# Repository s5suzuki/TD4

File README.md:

# TD4

- 「CPUの創りかた」のCPUの基板データとLチカプログラム
  - ROM部分は面倒なのでRaspberry Pi Picoで代用している

# Author

Shun Suzuki, 2023

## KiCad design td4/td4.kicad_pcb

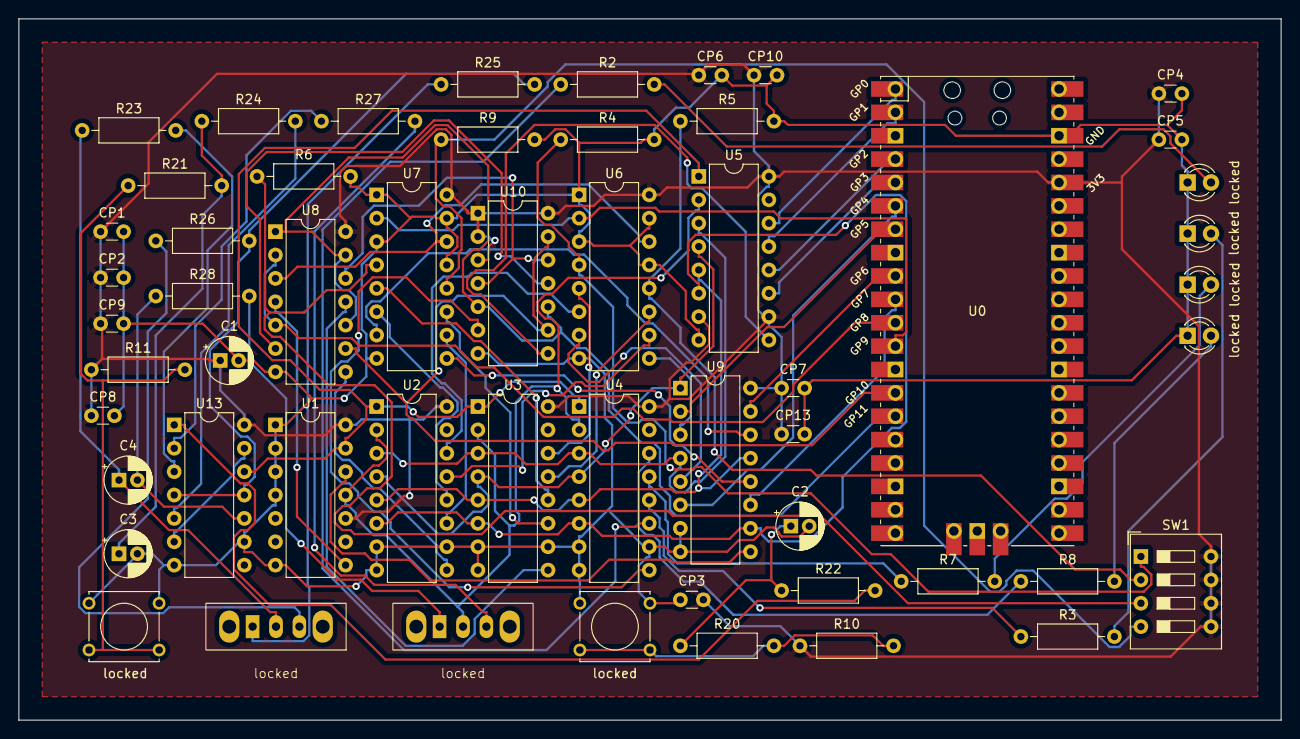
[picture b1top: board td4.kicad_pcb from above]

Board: 2 copper layers, 137.2 x 76.2 mm, 55 parts (0 on the bottom side), 69 nets.

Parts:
C1: 100u; CP_Radial_D5.0mm_P2.00mm
C2, C3, C4: 10u; CP_Radial_D5.0mm_P2.00mm
CP1, CP2, CP3, CP4, CP5, CP6, CP7, CP8, CP9, CP10, CP13: 0.1u; C_Disc_D3.0mm_W1.6mm_P2.50mm
R2, R3, R4, R5, R6, R7, R8, R9, R10, R11: 1k; R_Axial_DIN0207_L6.3mm_D2.5mm_P10.16mm_Horizontal
R20: 10k; R_Axial_DIN0207_L6.3mm_D2.5mm_P10.16mm_Horizontal
R21, R22, R23, R24: 100k; R_Axial_DIN0207_L6.3mm_D2.5mm_P10.16mm_Horizontal
R25: 3.3k; R_Axial_DIN0207_L6.3mm_D2.5mm_P10.16mm_Horizontal
R26: 33k; R_Axial_DIN0207_L6.3mm_D2.5mm_P10.16mm_Horizontal
R27, R28: 100; R_Axial_DIN0207_L6.3mm_D2.5mm_P10.16mm_Horizontal
SW1: SW_DIP_x04; SW_DIP_SPSTx04_Slide_9.78x12.34mm_W7.62mm_P2.54mm
U0: Pico; RPi_Pico_SMD_TH
U1: 74HC74; DIP-14_W7.62mm
U2, U3, U4, U5: 74LS161; DIP-16_W7.62mm
U6, U7: 74HC153; DIP-16_W7.62mm
U8: 74LS32; DIP-14_W7.62mm
U9: 74HC283; DIP-16_W7.62mm
U10: 74LS10; DIP-14_W7.62mm
U13: 74HC14; DIP-14_W7.62mm
locked: LED; LED_D3.0mm
locked#2, locked#5, locked#6: LED; LED_D3.0mm
locked#3, locked#7: SW_SPDT; Toggle_Switch
locked#4, locked#8: SW_MEC_5E; SW_Tactile_Straight_KSL0Axx1LFTR

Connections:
+3.3V: C1.1, CP1.1, CP2.1, CP3.2, CP4.1, CP5.1, CP6.1, CP7.1, CP8.1, CP9.1, CP10.1, CP13.1, R10.1, R11.1, SW1.5, SW1.6, SW1.7, SW1.8, U0.36 (3V3), U1.10 (~S), U1.14 (VCC), U2.16 (VCC), U3.16 (VCC), U4.16 (VCC), U5.7 (ENP), U5.10 (ENT), U5.16 (VCC), U6.16 (VCC), U7.16 (VCC), U8.14 (VCC), U9.16 (VCC), U10.1, U10.2, U10.3, U10.14 (VCC), U13.14 (VCC)
/clock_reset/CLOCK: U1.11 (C), U2.2 (CK), U3.2 (CK), U4.2 (CK), U5.2 (CK), locked#3.2 (B)
/clock_reset/RESET: U1.13 (~R), U2.1 (~CLR), U3.1 (~CLR), U4.1 (~CLR), U5.1 (~CLR), U13.12
/logic/A0: U0.1 (GPIO0), U5.14 (QA)
/logic/A1: U0.2 (GPIO1), U5.13 (QB)
/logic/A2: U0.4 (GPIO2), U5.12 (QC)
/logic/A3: U0.5 (GPIO3), U5.11 (QD)
/logic/D0: U0.6 (GPIO4), U9.6 (B1)
/logic/D1: U0.7 (GPIO5), U9.2 (B2)
/logic/D2: U0.9 (GPIO6), U9.15 (B3)
/logic/D3: U0.10 (GPIO7), U9.11 (B4)
/logic/D4: U0.11 (GPIO8), U8.2, U8.5
/logic/D5: U0.12 (GPIO9), U6.2 (B), U7.2 (B)
/logic/D6: U0.14 (GPIO10), U8.9, U10.9, U10.13
/logic/D7: U0.15 (GPIO11), U8.1, U8.10, U8.13, U10.5, U10.10
GND: C1.2, C2.2, C3.2, CP1.2, CP2.2, CP3.1, CP4.2, CP5.2, CP6.2, CP7.2, CP8.2, CP9.2, CP10.2, CP13.2, R4.2, R5.2, R6.2, R9.2, U0.38 (GND), U1.1 (~R), U1.2 (D), U1.3 (C), U1.4 (~S), U1.7 (GND), U2.7 (ENP), U2.8 (GND), U2.10 (ENT), U3.7 (ENP), U3.8 (GND), U3.10 (ENT), U4.7 (ENP), U4.8 (GND), U4.10 (ENT), U5.8 (GND), U6.1 (~1G), U6.3 (IC3), U6.8 (GND), U6.13 (2C3), U6.15 (~2G), U7.1 (~1G), U7.3 (IC3), U7.8 (GND), U7.13 (2C3), U7.15 (~2G), U8.7 (GND), U9.7 (C0), U9.8 (GND), U10.7 (GND), U13.7 (GND), U13.9, locked.1 (K), locked#2.1 (K), locked#4.1, locked#5.1 (K), locked#6.1 (K), locked#8.1
unnamed: C2.1, R20.1, R22.1
unnamed: C3.1, R21.2, R24.1
unnamed: C4.2, R28.1, U13.10
unnamed: R2.2, locked#5.2 (A)
unnamed: R3.2, locked.2 (A)
unnamed: R7.2, locked#2.2 (A)
unnamed: R8.2, locked#6.2 (A)
unnamed: R22.2, U13.1
unnamed: R23.2, U13.3
unnamed: R24.2, U13.5
unnamed: R25.2, R26.2, U13.4, U13.11
unnamed: R27.1, U13.2
unnamed: R10.2, R20.2, locked#8.2 (A)
unnamed: R11.2, R21.1, locked#4.2 (A)
unnamed: R25.1, locked#7.1 (A)
unnamed: C4.1, R23.1, locked#7.2 (B)
unnamed: R26.1, locked#7.3 (C)
unnamed: R28.2, locked#3.1 (A)
unnamed: R27.2, locked#3.3 (C)
unnamed: U1.12 (D), U9.9 (C4)
unnamed: U1.8 (~Q), U8.4
unnamed: U2.3 (A), U3.3 (A), U4.3 (A), U5.3 (A), U9.4 (S1)
unnamed: U2.4 (B), U3.4 (B), U4.4 (B), U5.4 (B), U9.1 (S2)
unnamed: U2.5 (C), U3.5 (C), U4.5 (C), U5.5 (C), U9.13 (S3)
unnamed: U2.6 (D), U3.6 (D), U4.6 (D), U5.6 (D), U9.10 (S4)
unnamed: U2.14 (QA), U6.6 (IC0)
unnamed: U2.13 (QB), U6.10 (2C0)
unnamed: U2.12 (QC), U7.6 (IC0)
unnamed: U2.11 (QD), U7.10 (2C0)
unnamed: U2.9 (~LOAD), U8.8
unnamed: U3.14 (QA), U6.5 (IC1)
unnamed: U3.13 (QB), U6.11 (2C1)
unnamed: U3.12 (QC), U7.5 (IC1)
unnamed: U3.11 (QD), U7.11 (2C1)
unnamed: U3.9 (~LOAD), U8.11
unnamed: R8.1, U4.14 (QA)
unnamed: R7.1, U4.13 (QB)
unnamed: R3.1, U4.12 (QC)
unnamed: R2.1, U4.11 (QD)
unnamed: U4.9 (~LOAD), U10.6
unnamed: U5.9 (~LOAD), U10.8
unnamed: U6.7 (1Y), U9.5 (A1)
unnamed: R5.1, SW1.2, U6.12 (2C2)
unnamed: U6.9 (2Y), U9.3 (A2)
unnamed: U6.14 (A), U7.14 (A), U8.3
unnamed: R4.1, SW1.1, U6.4 (IC2)
unnamed: U7.7 (1Y), U9.14 (A3)
unnamed: R9.1, SW1.4, U7.12 (2C2)
unnamed: U7.9 (2Y), U9.12 (A4)
unnamed: R6.1, SW1.3, U7.4 (IC2)
unnamed: U8.6, U10.11
unnamed: U8.12, U10.4, U10.12
unnamed: U13.6, U13.13

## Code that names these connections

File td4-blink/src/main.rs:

//! Blinks the LED on a Pico board
//!
//! This will blink an LED attached to GP25, which is the pin the Pico uses for the on-board LED.
#![no_std]
#![no_main]

use bsp::entry;
use defmt::*;
use defmt_rtt as _;
use embedded_hal::digital::v2::{InputPin, OutputPin};
use panic_probe as _;

// Provide an alias for our BSP so we can switch targets quickly.
// Uncomment the BSP you included in Cargo.toml, the rest of the code does not need to change.
use rp_pico as bsp;
// use sparkfun_pro_micro_rp2040 as bsp;

use bsp::hal::{
    clocks::{init_clocks_and_plls, Clock},
    pac,
    sio::Sio,
    watchdog::Watchdog,
};

#[entry]
fn main() -> ! {
    info!("Program start");
    let mut pac = pac::Peripherals::take().unwrap();
    let core = pac::CorePeripherals::take().unwrap();
    let mut watchdog = Watchdog::new(pac.WATCHDOG);
    let sio = Sio::new(pac.SIO);

    // External high-speed crystal on the pico board is 12Mhz
    let external_xtal_freq_hz = 12_000_000u32;
    let clocks = init_clocks_and_plls(
        external_xtal_freq_hz,
        pac.XOSC,
        pac.CLOCKS,
        pac.PLL_SYS,
        pac.PLL_USB,
        &mut pac.RESETS,
        &mut watchdog,
    )
    .ok()
    .unwrap();

    let mut delay = cortex_m::delay::Delay::new(core.SYST, clocks.system_clock.freq().to_Hz());

    let pins = bsp::Pins::new(
        pac.IO_BANK0,
        pac.PADS_BANK0,
        sio.gpio_bank0,
        &mut pac.RESETS,
    );

    // This is the correct pin on the Raspberry Pico board. On other boards, even if they have an
    // on-board LED, it might need to be changed.
    // Notably, on the Pico W, the LED is not connected to any of the RP2040 GPIOs but to the cyw43 module instead. If you have
    // a Pico W and want to toggle a LED with a simple GPIO output pin, you can connect an external
    // LED to one of the GPIO pins, and reference that pin here.
    let a0 = pins.gpio0.into_pull_up_input();
    let a1 = pins.gpio1.into_pull_up_input();
    let a2 = pins.gpio2.into_pull_up_input();
    let a3 = pins.gpio3.into_pull_up_input();

    let mut d0 = pins.gpio4.into_push_pull_output();
    let mut d1 = pins.gpio5.into_push_pull_output();
    let mut d2 = pins.gpio6.into_push_pull_output();
    let mut d3 = pins.gpio7.into_push_pull_output();
    let mut d4 = pins.gpio8.into_push_pull_output();
    let mut d5 = pins.gpio9.into_push_pull_output();
    let mut d6 = pins.gpio10.into_push_pull_output();
    let mut d7 = pins.gpio11.into_push_pull_output();

    let program: [u8; 16] = [
        0b10110011, 0b10110110, 0b10111100, 0b10111000, 0b10111000, 0b10111100, 0b10110110,
        0b10110011, 0b10110001, 0b11110000, 0b00000000, 0b00000000, 0b00000000, 0b00000000,
        0b00000000, 0b00000000,
    ];

    loop {
        let mut addr: usize = 0;
        addr |= if a0.is_high().unwrap() { 0x1 } else { 0x0 };
        addr |= if a1.is_high().unwrap() { 0x2 } else { 0x0 };
        addr |= if a2.is_high().unwrap() { 0x4 } else { 0x0 };
        addr |= if a3.is_high().unwrap() { 0x8 } else { 0x0 };

        let d = program[addr];
        if d & 0b00000001 == 0b00000001 {
            d0.set_high().unwrap();
        } else {
            d0.set_low().unwrap();
        }
        if d & 0b00000010 == 0b00000010 {
            d1.set_high().unwrap();
        } else {
            d1.set_low().unwrap();
        }
        if d & 0b00000100 == 0b00000100 {
            d2.set_high().unwrap();
        } else {
            d2.set_low().unwrap();
        }
        if d & 0b00001000 == 0b00001000 {
            d3.set_high().unwrap();
        } else {
            d3.set_low().unwrap();
        }
        if d & 0b00010000 == 0b00010000 {
            d4.set_high().unwrap();
        } else {
            d4.set_low().unwrap();
        }
        if d & 0b00100000 == 0b00100000 {
            d5.set_high().unwrap();
        } else {
            d5.set_low().unwrap();
        }
        if d & 0b01000000 == 0b01000000 {
            d6.set_high().unwrap();
        } else {
            d6.set_low().unwrap();
        }
        if d & 0b10000000 == 0b10000000 {
            d7.set_high().unwrap();
        } else {
            d7.set_low().unwrap();
        }
    }
}

// End of file

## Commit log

2023-04-23 init
2023-04-23 fix U5
2023-04-23 Create LICENSE
